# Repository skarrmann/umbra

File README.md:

# Umbra Keyboard

Umbra is a 24 key ergonomic keyboard, powered by a Raspberry Pi Pico.

There are enough keys for playing many games with a keyboard. 2D fighting games like Street Fighter was my personal intent for this build.

The board is a simple rectangle for increased sturdiness, which helps when placing the keyboard on your lap.

## Project structure

* [`gerbers`](gerbers): Gerber files for PCB manufacturing
* [`graphics`](graphics): Source assets for PCB silkscreen
* [`kicad`](kicad): KiCad project files (schematics and PCB designs)
* [`kicad-libraries`](kicad-libraries): KiCad components and footprints
* [`images`](images): Images for project documentation
* [`firmware`](firmware): Firmware files

## PCB

The PCB is designed for Kailh Choc v1 keyswitches, and supports keycaps designed for 18mm x 17mm spacing.

The Pi Pico footprint uses surface-mount solder pads. The castellated pads of the Pi Pico are used to solder it directly to the PCB.

The keyswitches are directly connected to the GPIO pins of the Pi Pico.

Each build uses two copies of the same PCB. This PCB acts as both the logical PCB, and when flipped the long way, it acts as a bottom plate to be attached the logical PCB.

## Keyboard firmware

* KMK
    * Setup instructions and basic configuration is in this repo: [`firmware/kmk`](firmware/kmk)
* GP2040-CE
    * Setup instructions in this repo: [`firmware/gp2040-ce`](firmware/gp2040-ce)

## Bill of materials

Part | Purpose | Quantity | Notes
---- | ------- | -------- | ---------
PCB  | circuit board and bottom plate | 2 | Send Gerber zip files to [JLCPCB](https://jlcpcb.com/).
Raspberry Pi Pico | Microcontroller board | 1 | Supports other boards with the Pico footprint and castellated solder pads (Waveshare RP2040 Plus) 
Keyswitches |  | 24 | Kailh Choc V1 keyswitches
Keycaps |  | 24 | Kailh Choc V1 keycaps (18mm x 17mm)
M2 6mm screws | Secure main PCB and bottom plate PCB | 7 |
M2 nuts | Secure main PCB and bottom plate PCB | 7 |
2mm tall rubber bumpons | Raise board above desk surface and provide skid resitance | 8 |

## PCB manufacturing settings

These are the manufacturing settings I used when ordering from JLCPCB:

* **Base Material**: FR4
* **Layers**: 2
* **Dimensions**: (whatever the gerber file specifies)
* **PCB Qty**: 5
* **Different Design**: 1
* **Delivery Format**: Single PCB
* **PCB Thickness**: 1.6
* **PCB Color**: Blue
* **Silkscreen**: White
* **Surface Finish**: LeadFree HASL-RoHS
* **Outer Copper Weight**: 1 oz
* **Gold Fingers**: No
* **Confirm Production File**: No
* **Flying Probe Test**: Fully Test
* **Castellated Holes**: No
* **Remove Order Number**: Specify a location

**IMPORTANT:** The PCB has ["JLCJLCJLCJLC" silkscreen text](https://support.jlcpcb.com/article/28-how-to-remove-order-number-from-your-pcb) on the bottom side of the board. If you want to remove the order number from the boards or you want to print the PCBs with another manufacturer, then I recommend removing this silkscreen text from the `.kicad_pcb` file, and then regenerate the Gerber files.

## Build tips

* Before starting, check if the PCBs are warped, and bend them to be perfectly flat before soldering.
* To secure the bottom plate PCB, you can use flat metal M2 screws instead. Or use double-sided tape to adhere the bottom plate PCB directly to the logical PCB.

## KiCad project notes

The keyswitch footprints have cutouts for their through-hole solder pads, rotated 180 degrees from the center of the footprint. On opposite halves of the PCB, the keyswitch footprints are rotated 180 degrees. This allows the cutouts to encase the solder pads when the PCB is flipped and used as a bottom plate.

This project contains KiCad footprints for both Choc and MX switches with these mounting cutouts. There are also footprints and symbols for other microcontroller boards with castellated pads considered for the design (Waveshare RP-2040 Zero and Seeed XIAO RP2040).

Here are guidelines for using Umbra's self-encasing PCB construction approach for your own designs:

* Choose a microcontroller board which has castellated pads. Place the microcontroller footprint at the exact center of the PCB.
    * If the microcontroller board has components soldered to its bottom side (e.g., the Waveshare RP2040 Zero), then make a cutout on the PCB in the space between the solder pads of the microcontroller board's footprint.
* Place keyswitches on the left and right sides of the board so they are perfectly symmetric with each other. On the right side of the board, rotate each keyswitch 180 degrees.
* Make the board's edge cuts perfectly symmetric the long way. Rectangles are cool, but so are curvy shapes that trace the contours of the keyswitches!

## Revision history

* Choc rev1 (2022-03-19)
    * Initial PCB design

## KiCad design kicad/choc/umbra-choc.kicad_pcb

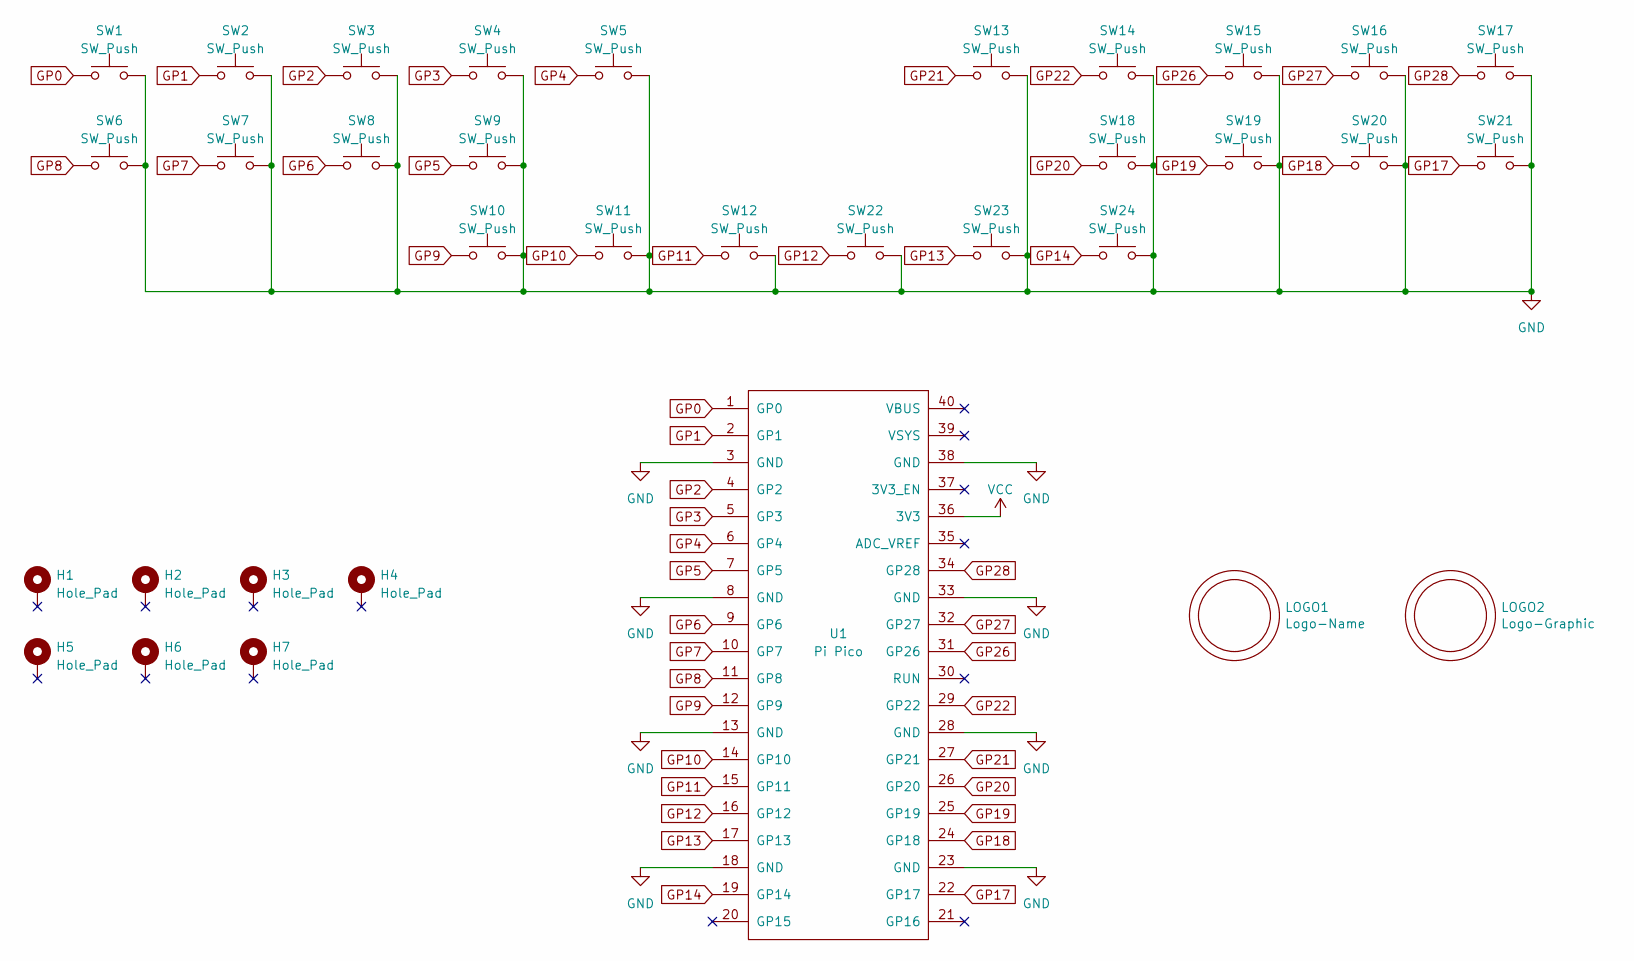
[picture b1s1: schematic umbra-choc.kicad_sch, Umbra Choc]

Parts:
H1, H2, H3, H4, H5, H6, H7: Hole_Pad; Mount_M2
LOGO1: Logo-Name; Logo_Umbra_Name
LOGO2: Logo-Graphic; Logo_Umbra
SW1, SW2, SW3, SW4, SW5, SW6, SW7, SW8, SW9, SW10, SW11, SW12, SW13, SW14, SW15, SW16, SW17, SW18, SW19, SW20, SW21, SW22, SW23, SW24: SW_Push; SW_Choc_Reverse_Cutout
U1: Pi Pico; Pi-Pico_SMD

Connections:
GND: SW1.2, SW2.2, SW3.2, SW4.2, SW5.2, SW6.2, SW7.2, SW8.2, SW9.2, SW10.2, SW11.2, SW12.2, SW13.2, SW14.2, SW15.2, SW16.2, SW17.2, SW18.2, SW19.2, SW20.2, SW21.2, SW22.2, SW23.2, SW24.2, U1.3 (GND), U1.8 (GND), U1.13 (GND), U1.18 (GND), U1.23 (GND), U1.28 (GND), U1.33 (GND), U1.38 (GND)
GP0: SW1.1, U1.1 (GP0)
GP1: SW2.1, U1.2 (GP1)
GP2: SW3.1, U1.4 (GP2)
GP3: SW4.1, U1.5 (GP3)
GP4: SW5.1, U1.6 (GP4)
GP5: SW9.1, U1.7 (GP5)
GP6: SW8.1, U1.9 (GP6)
GP7: SW7.1, U1.10 (GP7)
GP8: SW6.1, U1.11 (GP8)
GP9: SW10.1, U1.12 (GP9)
GP10: SW11.1, U1.14 (GP10)
GP11: SW12.1, U1.15 (GP11)
GP12: SW22.1, U1.16 (GP12)
GP13: SW23.1, U1.17 (GP13)
GP14: SW24.1, U1.19 (GP14)
GP17: SW21.1, U1.22 (GP17)
GP18: SW20.1, U1.24 (GP18)
GP19: SW19.1, U1.25 (GP19)
GP20: SW18.1, U1.26 (GP20)
GP21: SW13.1, U1.27 (GP21)
GP22: SW14.1, U1.29 (GP22)
GP26: SW15.1, U1.31 (GP26)
GP27: SW16.1, U1.32 (GP27)
GP28: SW17.1, U1.34 (GP28)
VCC: U1.36 (3V3)

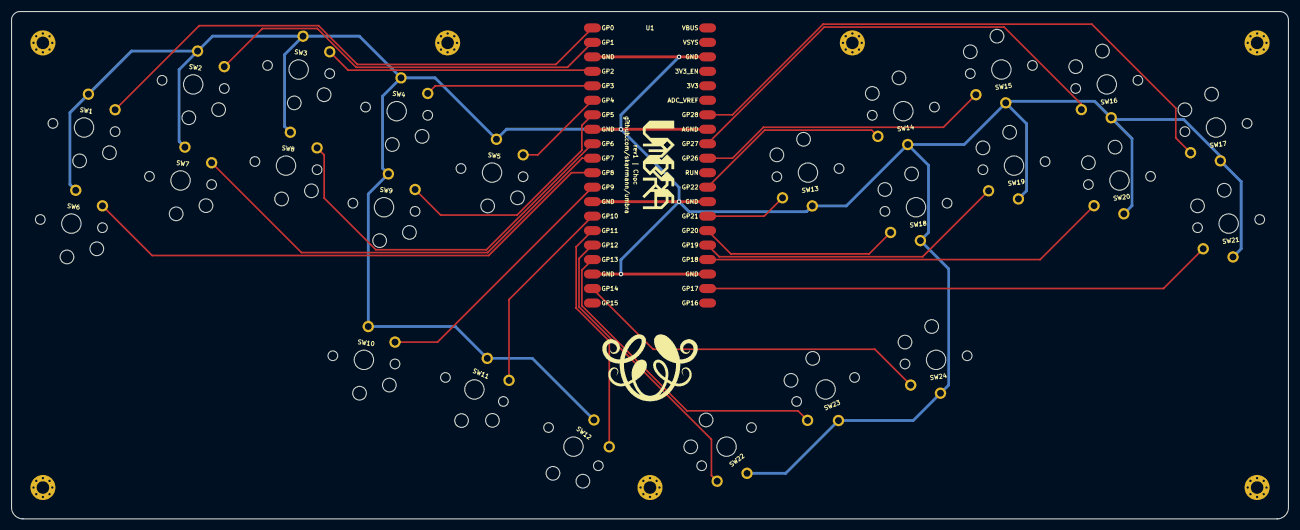
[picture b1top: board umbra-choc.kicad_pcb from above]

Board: 2 copper layers, 224.0 x 89.0 mm, 34 parts (0 on the bottom side), 25 nets.

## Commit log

2023-03-20 Create Choc rev1
2023-04-02 Write KMK firmware
2023-04-02 Complete initial readme with images
2023-04-02 Update license year
2023-04-05 Add 16:9 photos
2023-04-12 Update schematic global labels for GPIO assignment readability
2023-04-12 Add GP2040-CE firmware setup instructions
2023-11-02 Remove vendor URLs
